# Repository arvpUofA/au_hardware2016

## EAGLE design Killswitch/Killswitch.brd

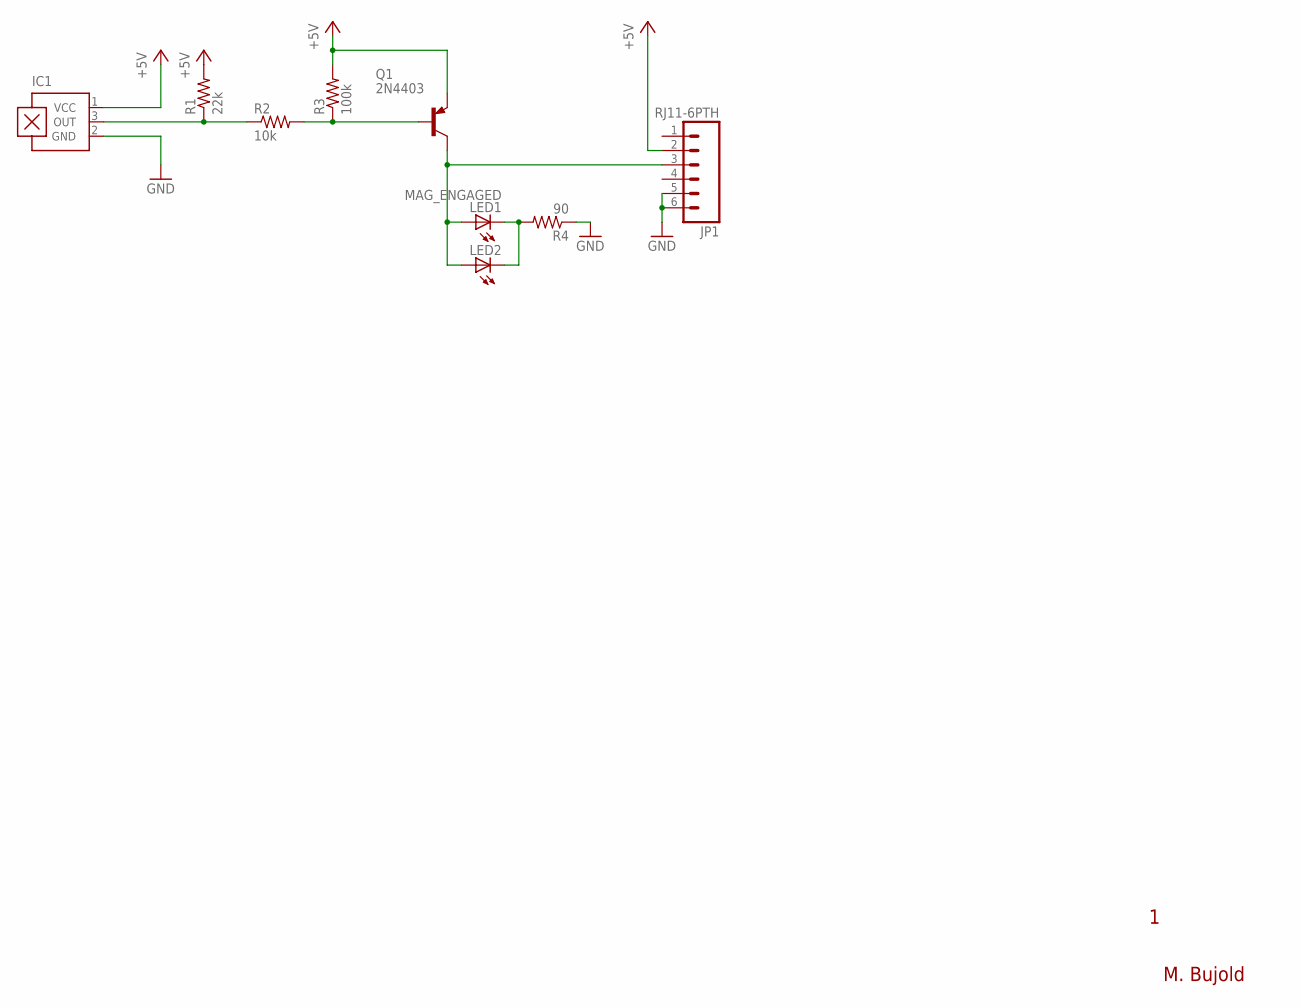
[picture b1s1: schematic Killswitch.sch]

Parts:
IC1: A1384UA; SIP3-UA
JP1: RJ11-6PTH; RJ11-6
LED1: MAG_ENGAGED; CHIPLED_1206
LED2: LED3MM
Q1: 2N4403; TO92
R1: 22k; 1206
R2: 10k; 1206
R3: 100k; 1206
R4: 90; 1206

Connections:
+5V: IC1.1 (VCC), JP1.2, Q1.3 (E), R1.2, R3.2
GND: IC1.2 (GND), JP1.5, JP1.6, R4.1
unnamed: IC1.3 (OUT), R1.1, R2.1
unnamed: Q1.2 (B), R2.2, R3.1
unnamed: LED1.C, LED2.K (C), R4.2
unnamed: JP1.3, LED1.A, LED2.A, Q1.1 (C)

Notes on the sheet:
M. Bujold

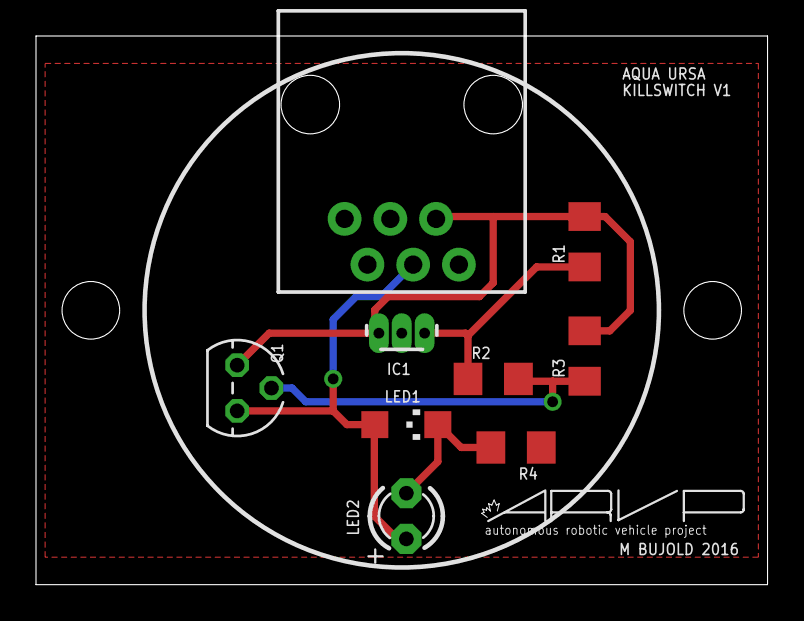
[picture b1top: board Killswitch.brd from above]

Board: 2 copper layers, 40.6 x 30.5 mm, 10 parts (0 on the bottom side), 6 nets.

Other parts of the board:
U$1: ARVP

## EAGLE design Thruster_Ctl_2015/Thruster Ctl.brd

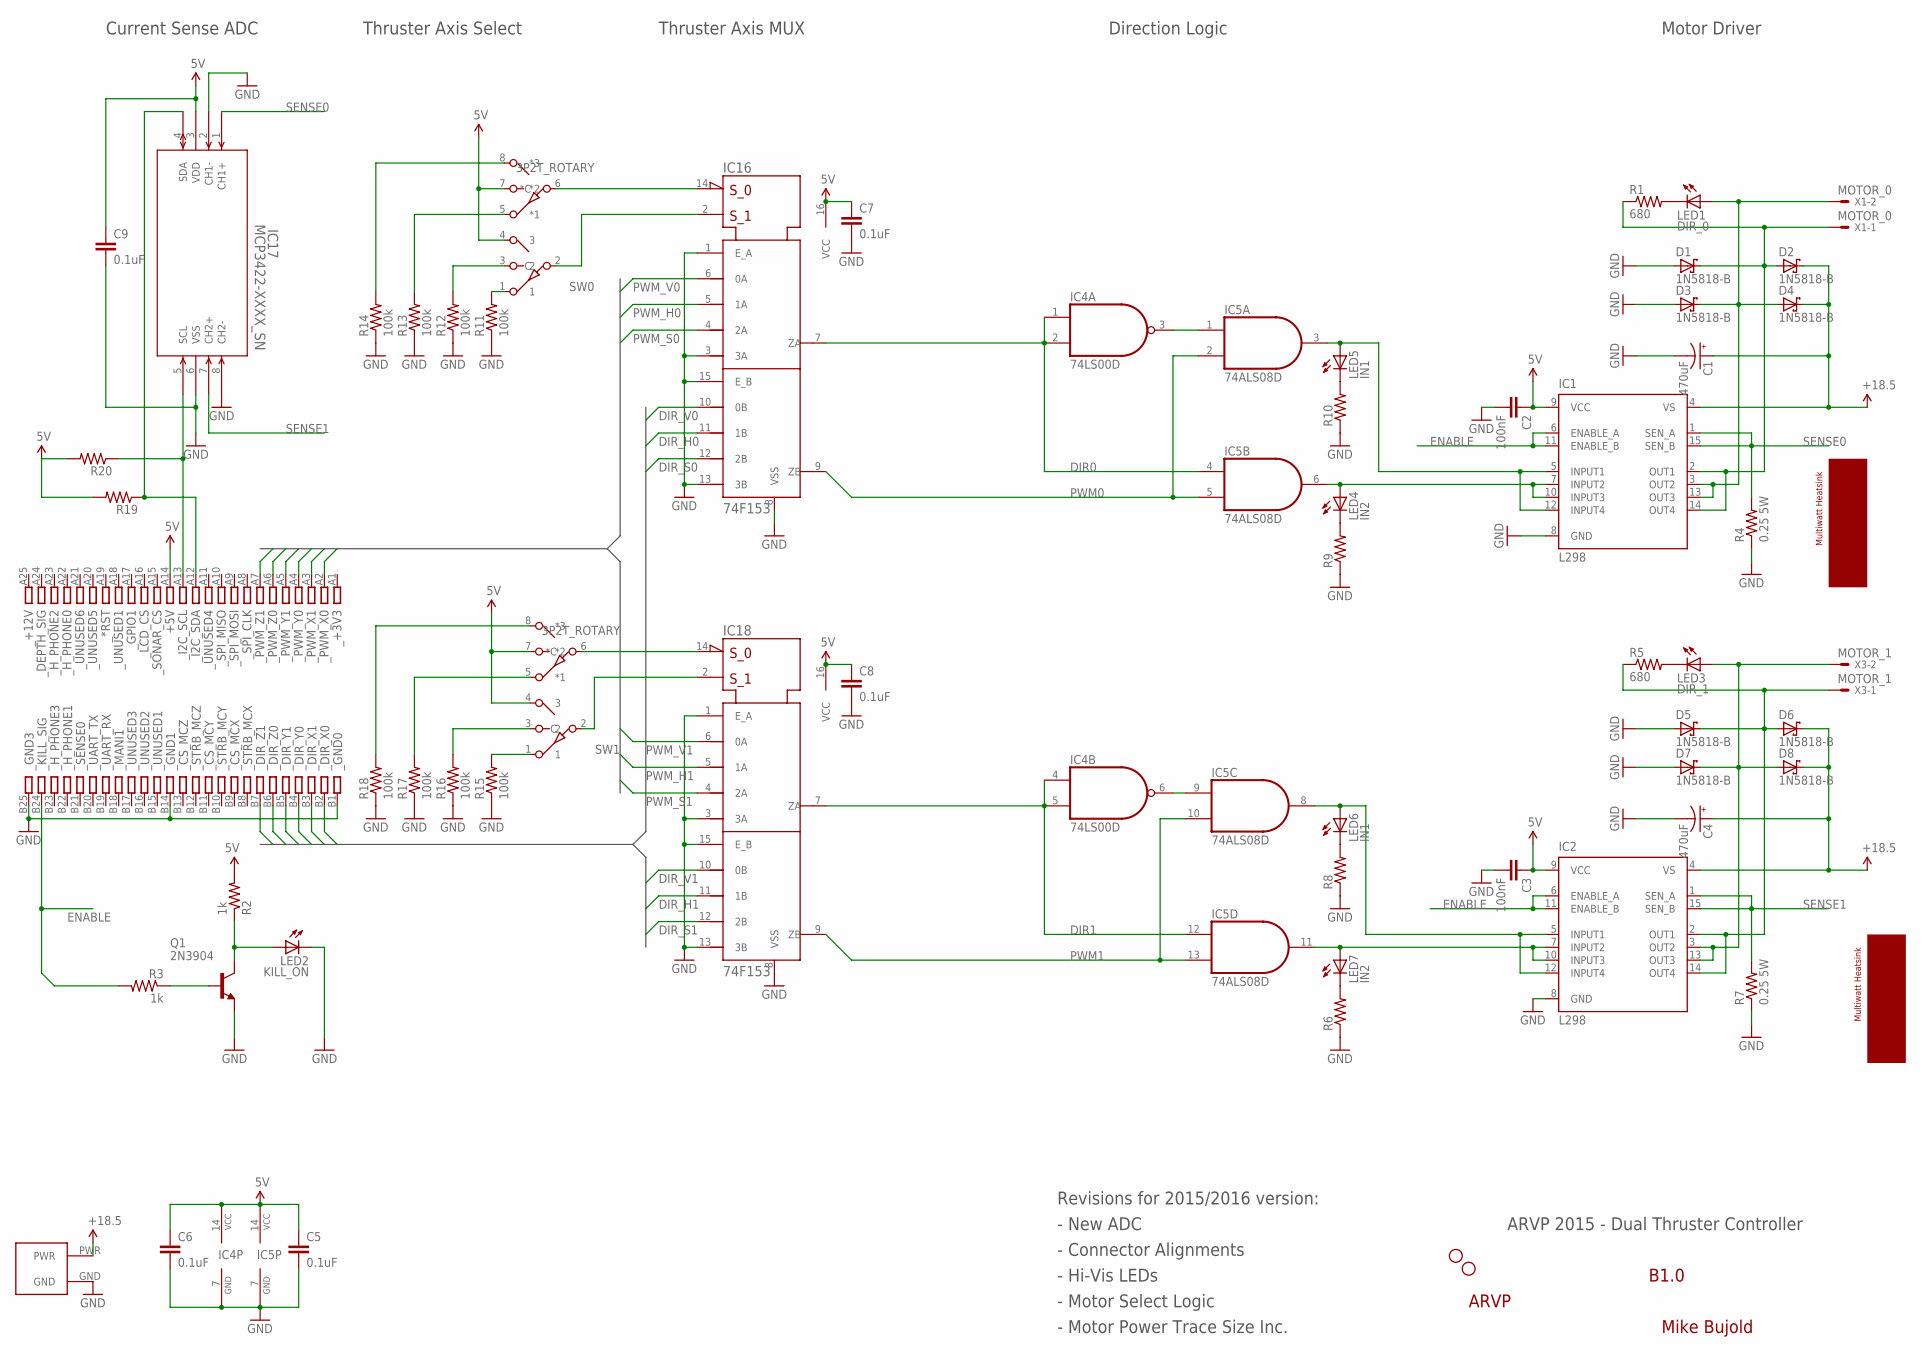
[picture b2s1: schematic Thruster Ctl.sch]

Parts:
C1, C4: 470uF; E25-10
C2, C3: 100nF; CAP-PTH-SMALL
C5, C6, C7, C8, C9: 0.1uF; 1206
D1, D2, D3, D4, D5, D6, D7, D8: 1N5818-B; DO41-7.6
IC1, IC2: L298; MULTIWATT-15
IC4: 74LS00D; SO14
IC5: 74ALS08D; SO14
IC16, IC18: 74F153; SO16
IC17: MCP3422-XXXX_SN; SOIC8-N_MC
JP1, JP4: STAND-OFF
LED1: DIR_0; LED5MM
LED2: KILL_ON; LED5MM
LED3: DIR_1; LED5MM
LED4, LED7: IN2; 1206
LED5, LED6: IN1; 1206
Q1: 2N3904; TO92
R1, R5: 680; AXIAL-0.4
R2, R3: 1k; AXIAL-0.4
R4, R7: 0.25 5W; 0922/22
R6, R8, R9, R10, R19, R20: RESISTOR1206; 1206
R11, R12, R13, R14, R15, R16, R17, R18: 100k; 1206
SW0, SW1: 3P2T_ROTARY; DIL08
U$4: ARVP_LOGO; ARVP
U$7: AND_PWR
U$9, U$10: L298_HS; HEATSINK_MW
U$19: CARD_50PIN
X1: MOTOR_0; KK-156-2
X3: MOTOR_1; KK-156-2

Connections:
5V: C2.1, C3.1, C5.1, C6.1, C7.1, C8.1, C9.1, IC1.9 (VCC), IC2.9 (VCC), IC4.14 (VCC), IC5.14 (VCC), IC16.16 (VCC), IC17.3 (VDD), IC18.16 (VCC), R2.P$2 (2), R19.2, R20.2, SW0.4 (3), SW0.7 (*2), SW1.4 (3), SW1.7 (*2), U$19.A14
18.5V: C1.+, C4.+, D2.C, D4.C, D6.C, D8.C, IC1.4 (VS), IC2.4 (VS), U$7.PWR
DIR0: IC4.1 (I0), IC4.2 (I1), IC5.4 (I0), IC16.7 (ZA)
DIR1: IC4.4 (I0), IC4.5 (I1), IC5.12 (I0), IC18.7 (ZA)
DIR_H0: IC16.11 (1B), U$19.B4
DIR_H1: IC18.11 (1B), U$19.B5
DIR_S0: IC16.12 (2B), U$19.B6
DIR_S1: IC18.12 (2B), U$19.B7
DIR_V0: IC16.10 (0B), U$19.B2
DIR_V1: IC18.10 (0B), U$19.B3
ENABLE: IC1.6 (ENABLE_A), IC1.11 (ENABLE_B), IC2.6 (ENABLE_A), IC2.11 (ENABLE_B), R3.P$2 (2), U$19.B24
GND: C1.-, C2.2, C3.2, C4.-, C5.2, C6.2, C7.2, C8.2, C9.2, D1.A, D3.A, D5.A, D7.A, IC1.8 (GND), IC2.8 (GND), IC4.7 (GND), IC5.7 (GND), IC16.1 (E_A), IC16.3 (3A), IC16.8 (VSS), IC16.13 (3B), IC16.15 (E_B), IC17.2 (CH1-), IC17.6 (VSS), IC17.8 (CH2-), IC18.1 (E_A), IC18.3 (3A), IC18.8 (VSS), IC18.13 (3B), IC18.15 (E_B), LED2.K (C), Q1.3 (E), R4.1, R6.1, R7.1, R8.1, R9.1, R10.1, R11.1, R12.1, R13.1, R14.1, R15.1, R16.1, R17.1, R18.1, U$7.GND, U$19.B1, U$19.B14, U$19.B25
unnamed: IC16.14 (S0), SW0.6 (*C)
unnamed: R13.2, SW0.5 (*1)
unnamed: LED2.A, Q1.1 (C), R2.P$1 (1)
unnamed: IC2.5 (INPUT1), IC2.12 (INPUT4), IC5.8 (O), LED6.A
unnamed: IC1.5 (INPUT1), IC1.12 (INPUT4), IC5.3 (O), LED5.A
unnamed: IC1.7 (INPUT2), IC1.10 (INPUT3), IC5.6 (O), LED4.A
unnamed: D1.C, D2.A, IC1.2 (OUT1), IC1.14 (OUT4), R1.P$1 (1), X1.1
unnamed: D3.C, D4.A, IC1.3 (OUT2), IC1.13 (OUT3), LED1.A, X1.2
unnamed: LED1.K (C), R1.P$2 (2)
unnamed: IC18.14 (S0), SW1.6 (*C)
unnamed: D5.C, D6.A, IC2.2 (OUT1), IC2.14 (OUT4), R5.P$1 (1), X3.1
unnamed: D7.C, D8.A, IC2.3 (OUT2), IC2.13 (OUT3), LED3.A, X3.2
unnamed: R11.2, SW0.1
unnamed: LED3.K (C), R5.P$2 (2)
unnamed: IC16.2 (S1), SW0.2 (C)
unnamed: IC18.2 (S1), SW1.2 (C)
unnamed: LED7.C, R6.2
unnamed: LED6.C, R8.2
unnamed: LED4.C, R9.2
unnamed: LED5.C, R10.2
unnamed: IC17.5 (SCL), R20.1, U$19.A13
unnamed: IC17.4 (SDA), R19.1, U$19.A12
unnamed: R12.2, SW0.3 (2)
unnamed: IC4.6 (O), IC5.9 (I0)
unnamed: R14.2, SW0.8 (*3)
unnamed: IC4.3 (O), IC5.1 (I0)
unnamed: Q1.2 (B), R3.P$1 (1)
unnamed: IC2.7 (INPUT2), IC2.10 (INPUT3), IC5.11 (O), LED7.A
unnamed: R17.2, SW1.5 (*1)
unnamed: R15.2, SW1.1
unnamed: R16.2, SW1.3 (2)
unnamed: R18.2, SW1.8 (*3)
PWM0: IC5.2 (I1), IC5.5 (I1), IC16.9 (ZB)
PWM1: IC5.10 (I1), IC5.13 (I1), IC18.9 (ZB)
PWM_H0: IC16.5 (1A), U$19.A4
PWM_H1: IC18.5 (1A), U$19.A5
PWM_S0: IC16.4 (2A), U$19.A6
PWM_S1: IC18.4 (2A), U$19.A7
PWM_V0: IC16.6 (0A), U$19.A2
PWM_V1: IC18.6 (0A), U$19.A3
SENSE0: IC1.1 (SEN_A), IC1.15 (SEN_B), IC17.1 (CH1+), R4.2
SENSE1: IC2.1 (SEN_A), IC2.15 (SEN_B), IC17.7 (CH2+), R7.2

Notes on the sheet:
ARVP 2015 - Dual Thruster Controller
Mike Bujold
B1.0
Revisions for 2015/2016 version:
- New ADC
- Connector Alignments
- Hi-Vis LEDs
- Motor Select Logic
Thruster Axis MUX
Direction Logic
Motor Driver
- Motor Power Trace Size Inc.
Thruster Axis Select
Current Sense ADC

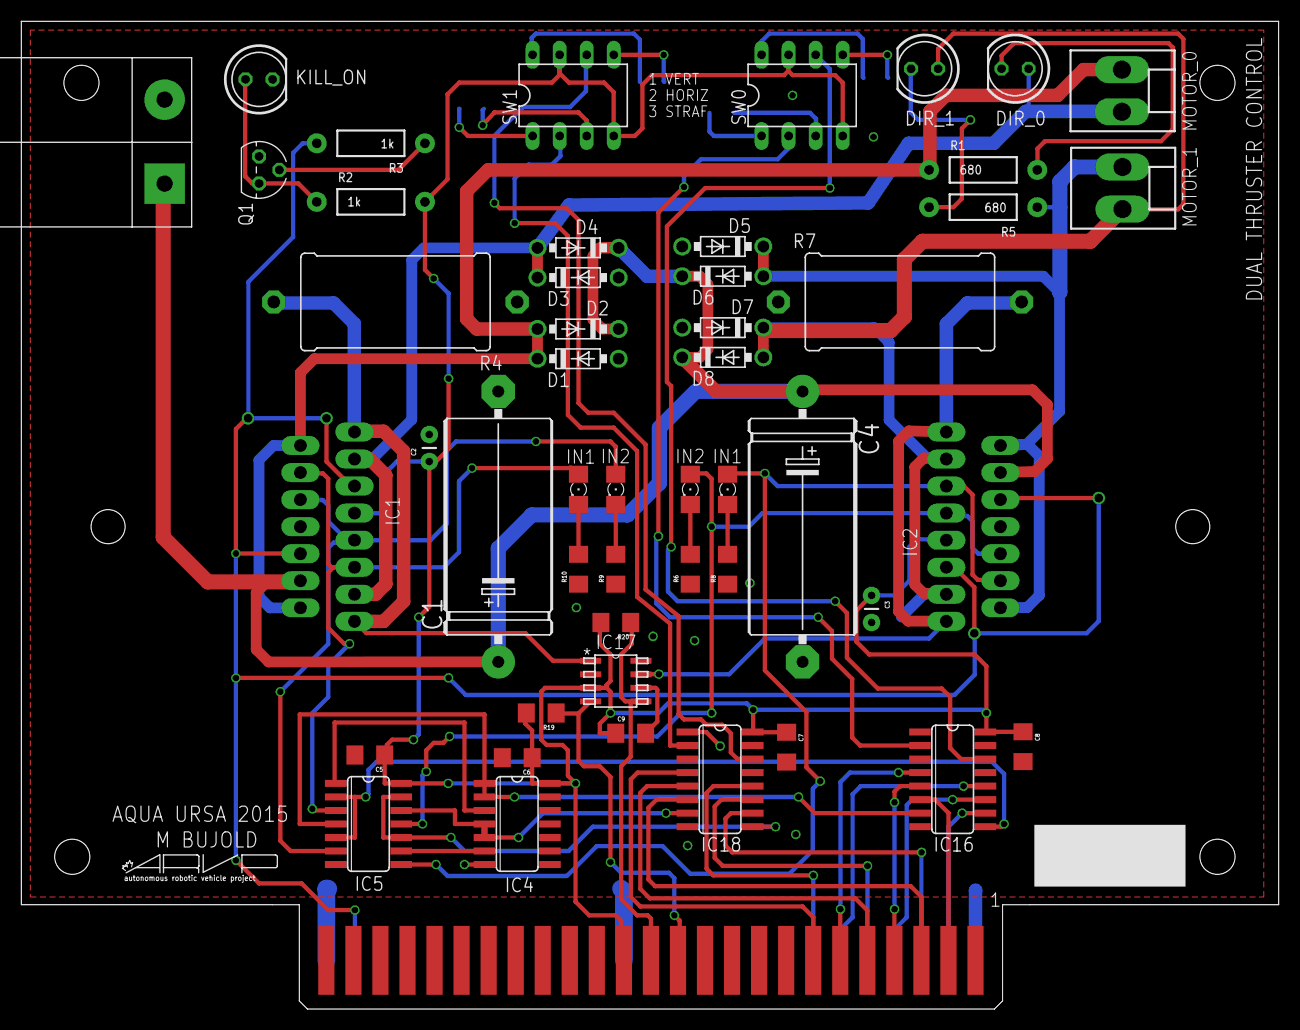
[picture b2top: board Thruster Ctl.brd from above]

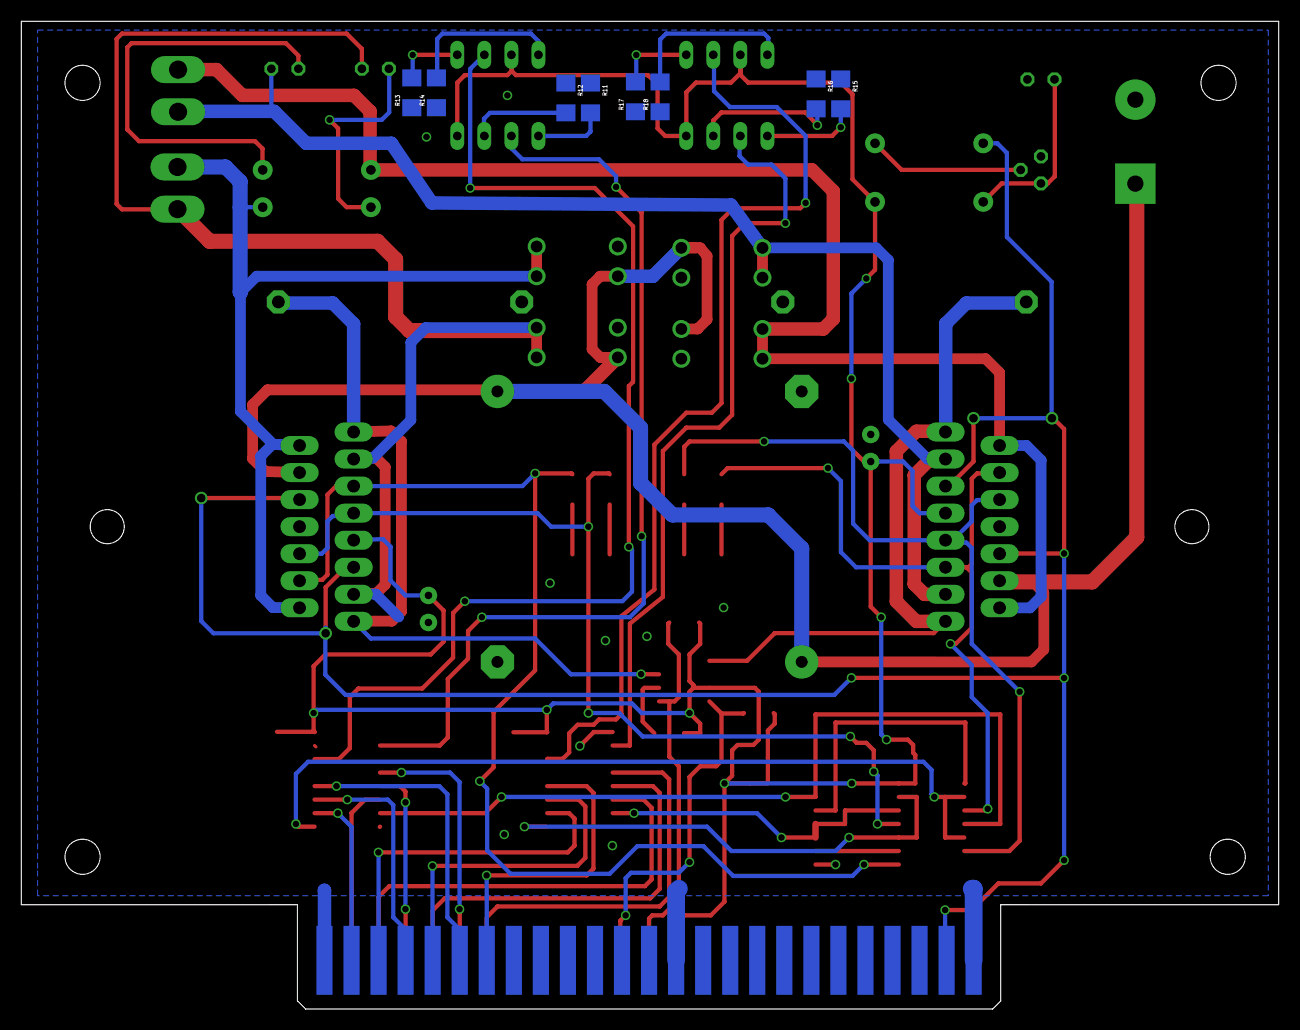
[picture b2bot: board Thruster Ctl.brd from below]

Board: 2 copper layers, 118.1 x 92.8 mm, 65 parts (8 on the bottom side), 54 nets.

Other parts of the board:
JP2, JP3: STAND-OFF

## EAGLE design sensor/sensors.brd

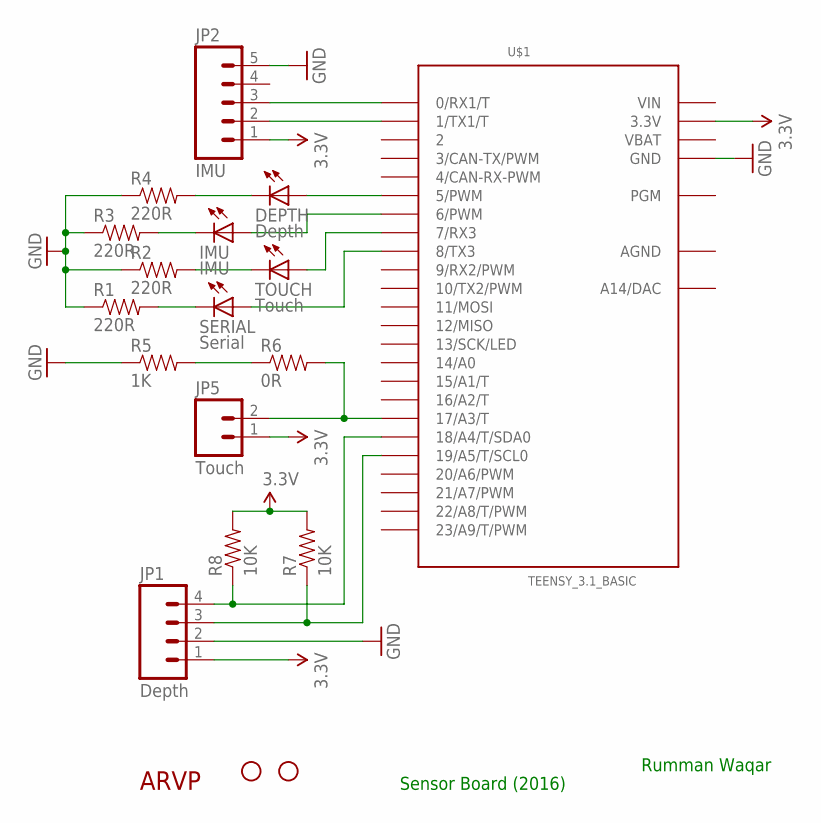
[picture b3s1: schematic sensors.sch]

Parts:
DEPTH: Depth; LED-1206
IMU: IMU; LED-1206
JP1: Depth; 1X04_LONGPADS
JP2: IMU; 1X05_LONGPADS
JP3, JP4: STAND-OFF
JP5: Touch; MOLEX-1X2
R1, R2, R3, R4: 220R; 1206
R5: 1K; 1206
R6: 0R; 1206
R7, R8: 10K; 0805
SERIAL: Serial; LED-1206
TOUCH: Touch; LED-1206
U$1: TEENSY_3.1_BASIC
U$2: ARVP_LOGO; ARVP

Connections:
3.3V: JP1.1, JP2.1, JP5.1, R7.2, R8.2, U$1.3.3V, U$1.3.3V1 (3.3V)
AGND: U$1.AGND
GND: JP1.2, JP2.5, R1.1, R2.1, R3.1, R4.1, R5.1, U$1.GND, U$1.GND1 (GND)
unnamed: DEPTH.A, U$1.5 (5/PWM)
unnamed: DEPTH.C, R4.2
unnamed: IMU.C, R3.2
unnamed: R2.2, TOUCH.C
unnamed: R1.2, SERIAL.C
unnamed: IMU.A, U$1.6 (6/PWM)
unnamed: TOUCH.A, U$1.7 (7/RX3)
unnamed: SERIAL.A, U$1.8 (8/TX3)
unnamed: JP2.2, U$1.1 (1/TX1/T)
unnamed: JP2.3, U$1.0 (0/RX1/T)
unnamed: JP5.2, R6.2, U$1.17/A3 (17/A3/T)
unnamed: R5.2, R6.1
unnamed: JP1.3, R7.1, U$1.19/A5 (19/A5/T/SCL0)
unnamed: JP1.4, R8.1, U$1.18/A4 (18/A4/T/SDA0)
VBAT: U$1.VBAT
VIN: U$1.VIN

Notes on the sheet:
Rumman Waqar
Sensor Board (2016)

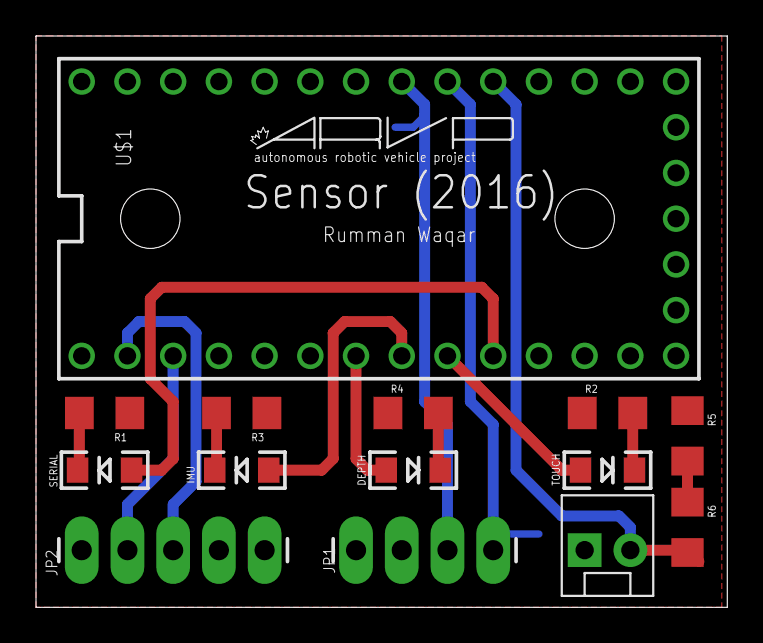
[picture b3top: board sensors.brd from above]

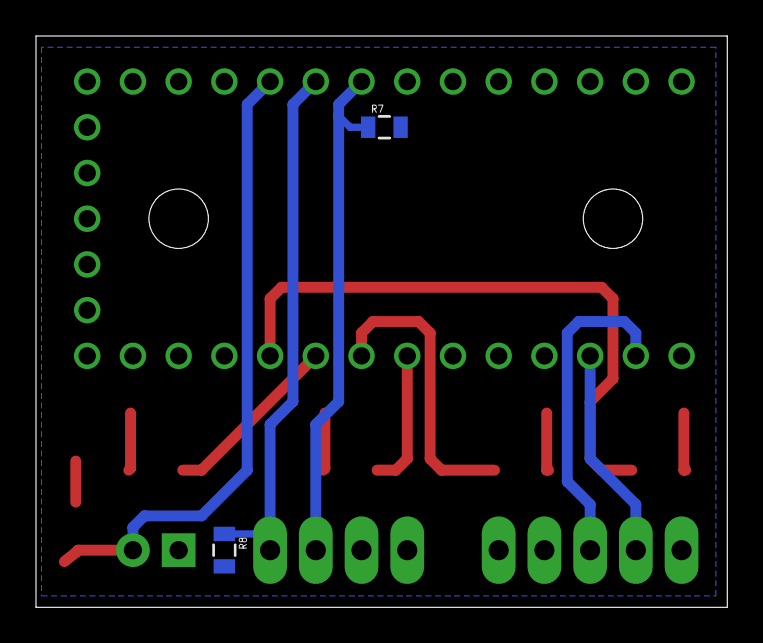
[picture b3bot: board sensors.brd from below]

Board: 2 copper layers, 38.4 x 31.7 mm, 19 parts (2 on the bottom side), 16 nets.

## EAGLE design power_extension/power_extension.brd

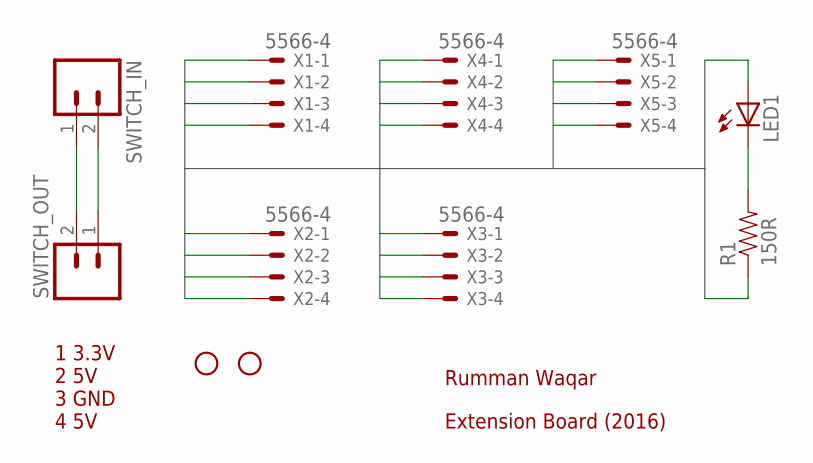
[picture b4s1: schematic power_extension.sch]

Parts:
JP1, JP2: STAND-OFF
LED1: LED-FKIT-1206; FKIT-LED-1206
R1: 150R; 0805
SWITCH_IN: M02POLAR; MOLEX-1X2
SWITCH_OUT: M02POLAR; MOLEX-1X2
X1, X2, X3, X4, X5: 5566-4

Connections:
unnamed: SWITCH_IN.1, SWITCH_OUT.2
unnamed: SWITCH_IN.2, SWITCH_OUT.1
unnamed: LED1.C, R1.2
P1: X1.1, X2.1, X3.1, X4.1, X5.1
P2: X1.2, X2.2, X3.2, X4.2, X5.2
P3: R1.1, X1.3, X2.3, X3.3, X4.3, X5.3
P4: LED1.A, X1.4, X2.4, X3.4, X4.4, X5.4

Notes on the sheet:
1 3.3V 2 5V 3 GND 4 5V
Extension Board (2016)
Rumman Waqar

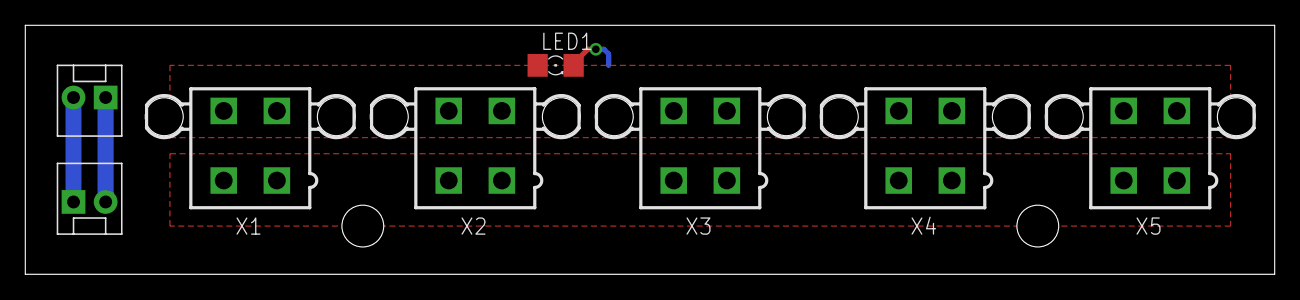
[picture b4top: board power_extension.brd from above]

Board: 2 copper layers, 98.7 x 19.7 mm, 11 parts (1 on the bottom side), 7 nets.

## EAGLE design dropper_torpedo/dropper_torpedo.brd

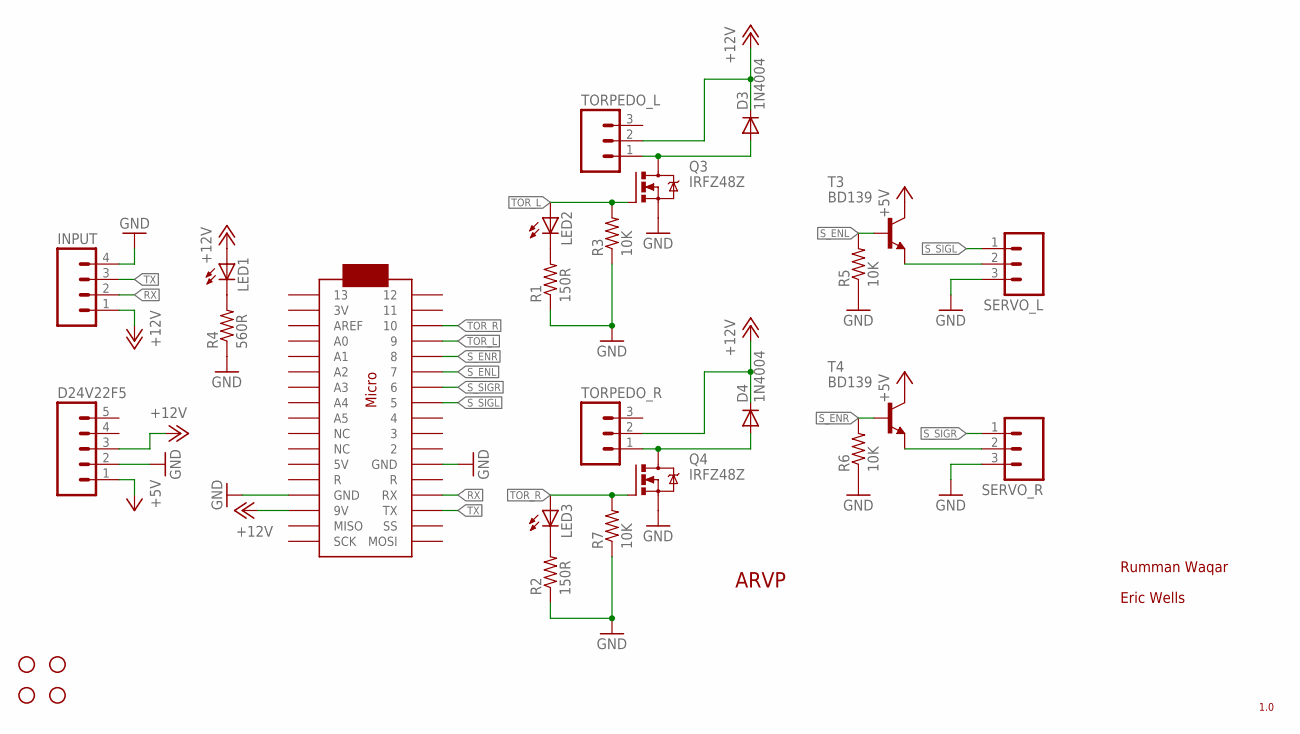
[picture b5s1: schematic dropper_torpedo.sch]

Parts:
D3, D4: 1N4004; DO41-10
D24V22F5: M05PTH; 1X05
INPUT: M04POLAR; MOLEX-1X4
JP1, JP2, JP3, JP4: STAND-OFF
LED1, LED2, LED3: LED0603; LED-0603
Q3, Q4: IRFZ48Z; TO220BH
R1, R2: 150R; 0805
R3, R5, R6, R7: 10K; 0805
R4: 560R; 0805
SERVO_L: M03POLAR; MOLEX-1X3
SERVO_R: M03POLAR; MOLEX-1X3
T3, T4: BD139; TO126
TORPEDO_L: M03POLAR; MOLEX-1X3
TORPEDO_R: M03POLAR; MOLEX-1X3
U$1: ARVP_LOGO; ARVP
U$2: ARDUINOMICRO

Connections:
+5V: D24V22F5.1, T3.2 (C), T4.2 (C)
+12V: D3.C, D4.C, D24V22F5.3, INPUT.1, LED1.A, TORPEDO_L.2, TORPEDO_R.2, U$2.P$20 (9V)
GND: D24V22F5.2, INPUT.4, Q3.S, Q4.S, R1.1, R2.1, R3.1, R4.1, R5.1, R6.1, R7.1, SERVO_L.3, SERVO_R.3, U$2.P$12 (GND), U$2.P$21 (GND)
unnamed: D3.A, Q3.D, TORPEDO_L.1
unnamed: LED2.C, R1.2
unnamed: D4.A, Q4.D, TORPEDO_R.1
unnamed: LED3.C, R2.2
unnamed: LED1.C, R4.2
unnamed: SERVO_L.2, T3.1 (E)
unnamed: SERVO_R.2, T4.1 (E)
RX: INPUT.2, U$2.P$14 (RX)
S_ENL: R5.2, T3.3 (B), U$2.P$6 (7)
S_ENR: R6.2, T4.3 (B), U$2.P$5 (8)
S_SIGL: SERVO_L.1, U$2.P$8 (5)
S_SIGR: SERVO_R.1, U$2.P$7 (6)
TOR_L: LED2.A, Q3.G, R3.2, U$2.P$4 (9)
TOR_R: LED3.A, Q4.G, R7.2, U$2.P$3 (10)
TX: INPUT.3, U$2.P$15 (TX)

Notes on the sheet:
1.0
Rumman Waqar
Eric Wells

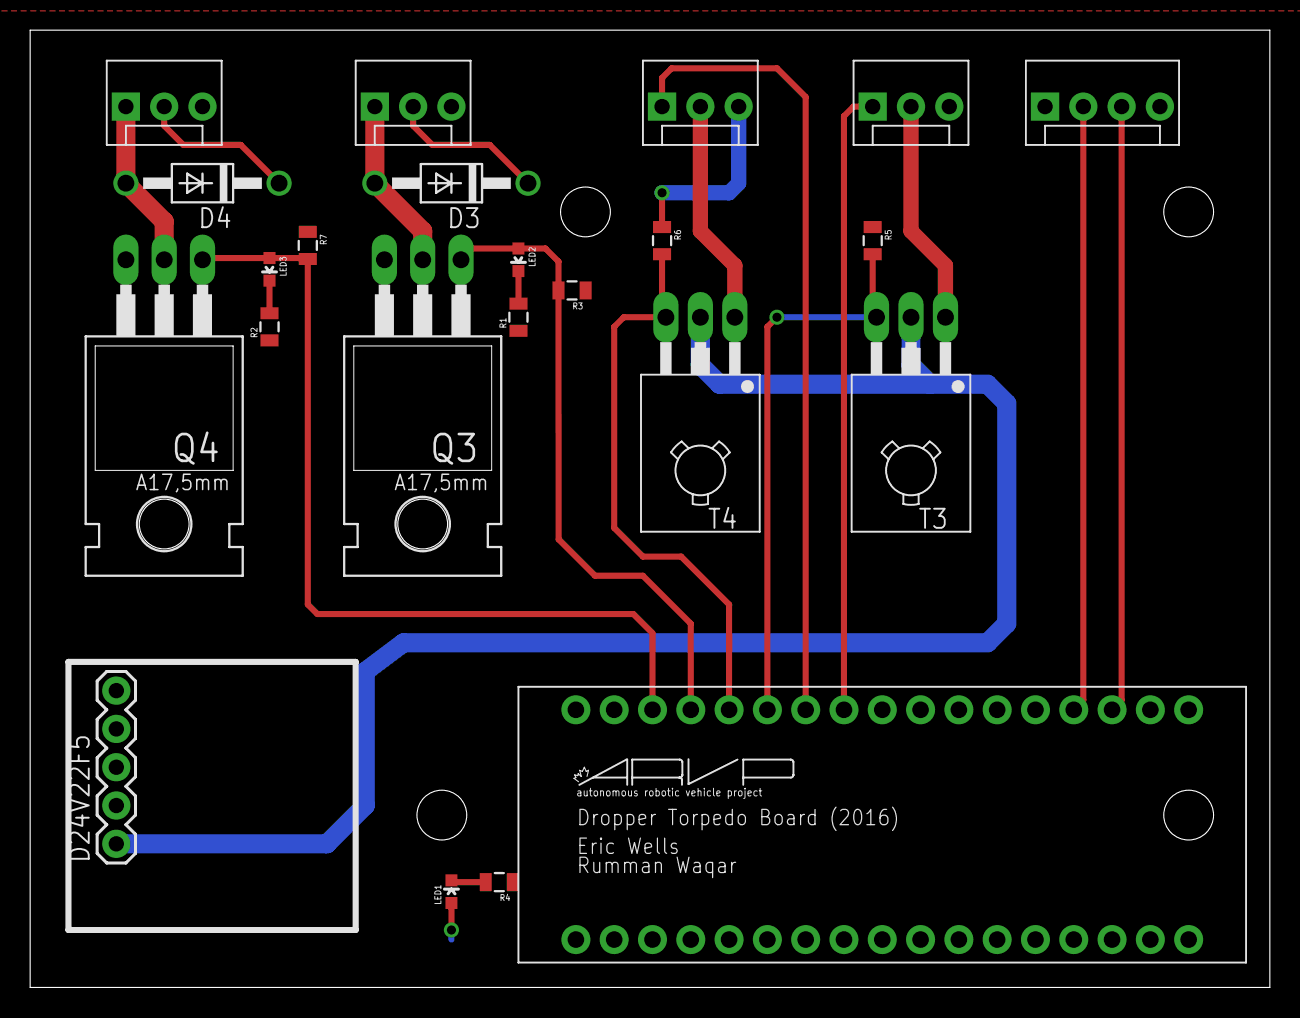
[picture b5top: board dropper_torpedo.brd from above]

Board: 2 copper layers, 82.2 x 63.5 mm, 28 parts (0 on the bottom side), 18 nets.

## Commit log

2016-07-13 Added libraries
2016-07-17 Completed sensor board changes
2016-07-17 Added power extension board
2016-07-17 Complete dropper torpedo board
2016-07-18 added apc cam rules
2016-07-18 Added dropper cam files
2016-07-18 power extension cam files
2016-07-18 fixed torpedo drill file
2016-07-18 added sensor cam files
2016-07-18 Fixed silkscreen for sensor
2016-07-18 Cam job file drill fix
2016-07-21 Added updated thruster controller and killswitch board/schematic

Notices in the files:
parts and their libraries:
SparkFun-Passives: Licensing: CC v3.0 Share-Alike You are welcome to use this library for commercial purposes.
